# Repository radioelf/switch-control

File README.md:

# switch-control

switch-control/Crossover switch (Kicad Versión: 5.99.0, release build)

Interruptor, conmutador (doble), cruzamiento, controlado con un modulo ESP8266, lo estoy usando con Tasmota (https://github.com/arendst/Tasmota), con la siguiente configuración:
D2 GPIO4  Botón1in (126)
D1 GPIO5  Llave1n (82)
D6 GPIO12 Relé1 (21)
D7 GPIO13 Led1 (53)

Creative Commons License Disclaimer

UNLESS OTHERWISE MUTUALLY AGREED TO BY THE PARTIES IN WRITING, LICENSOR OFFERS THE WORK AS-IS AND MAKES NO REPRESENTATIONS OR WARRANTIES OF ANY KIND CONCERNING THE WORK, EXPRESS, IMPLIED, STATUTORY OR OTHERWISE, INCLUDING, WITHOUT LIMITATION, WARRANTIES OF TITLE, MERCHANTIBILITY, FITNESS FOR A PARTICULAR PURPOSE, NONINFRINGEMENT, OR THE ABSENCE OF LATENT OR OTHER DEFECTS, ACCURACY, OR THE PRESENCE OF ABSENCE OF ERRORS, WHETHER OR NOT DISCOVERABLE. SOME JURISDICTIONS DO NOT ALLOW THE EXCLUSION OF IMPLIED WARRANTIES, SO SUCH EXCLUSION MAY NOT APPLY TO YOU. EXCEPT TO THE EXTENT REQUIRED BY APPLICABLE LAW, IN NO EVENT WILL LICENSOR BE LIABLE TO YOU ON ANY LEGAL THEORY FOR ANY SPECIAL, INCIDENTAL, CONSEQUENTIAL, PUNITIVE OR EXEMPLARY DAMAGES ARISING OUT OF THIS LICENSE OR THE USE OF THE WORK, EVEN IF LICENSOR HAS BEEN ADVISED OF THE POSSIBILITY OF SUCH DAMAGES.

http://creativecommons.org/licenses/by-sa/3.0/

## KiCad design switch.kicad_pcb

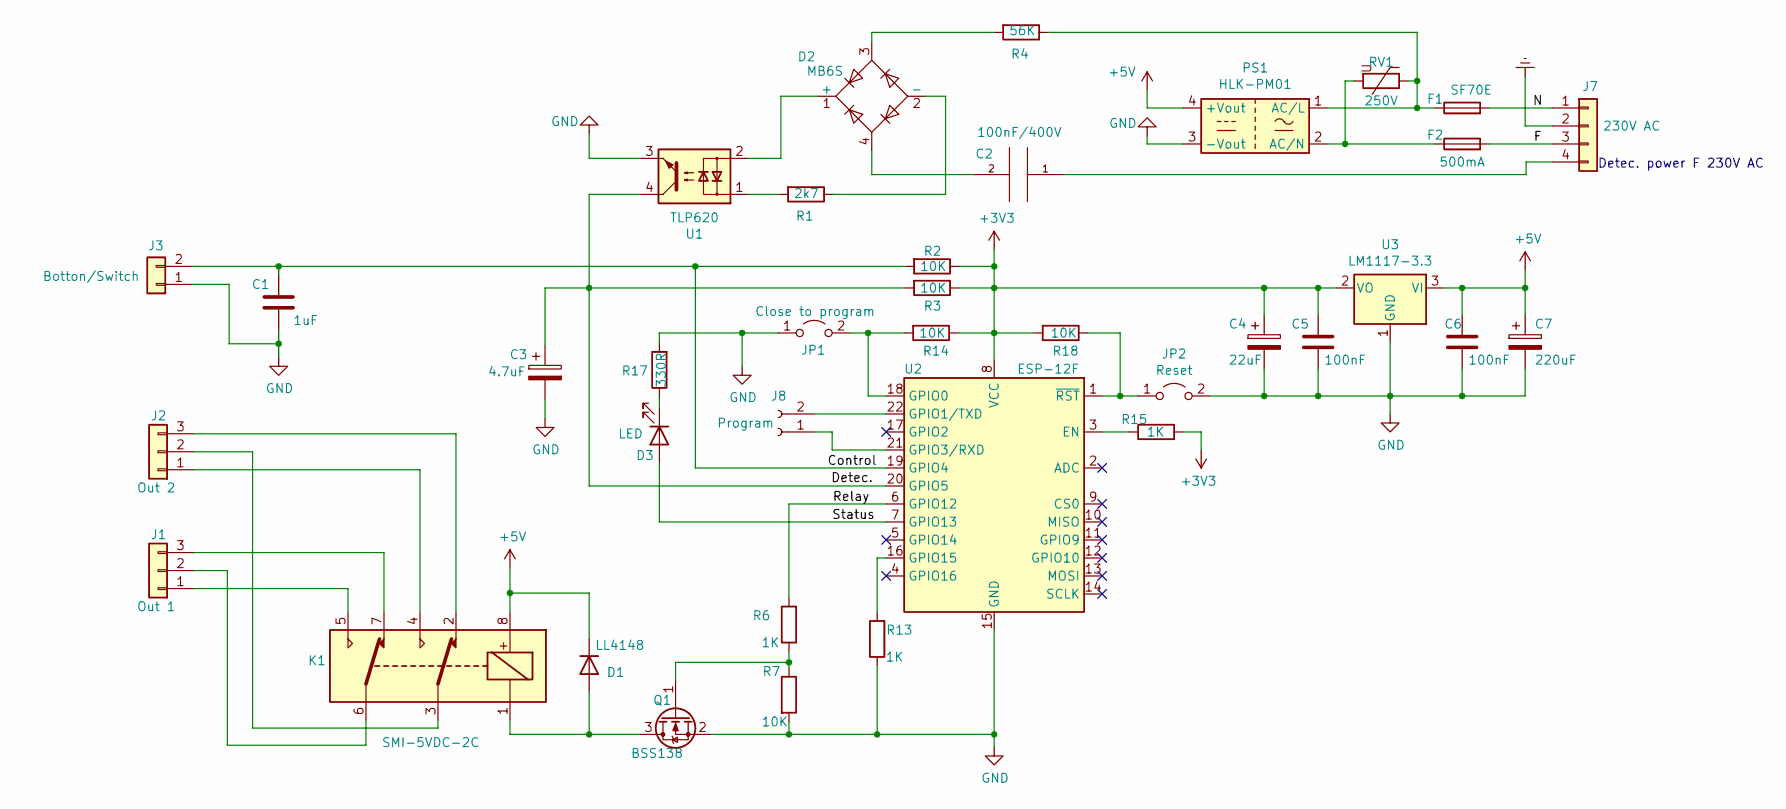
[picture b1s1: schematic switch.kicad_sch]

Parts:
C1: 1uF; C_1210_3225Metric
C2: 100nF/400V; C_Disc_D16.0mm_W5.0mm_P10.00mm
C3: 4.7uF; CP_Elec_4x3.9
C4: 22uF; CP_Elec_4x5.8
C5, C6: 100nF; L_0805_2012Metric_Pad1.15x1.40mm_HandSolder
C7: 220uF; CP_Elec_5x4.4
D1: LL4148; D_MiniMELF
D2: MB6S; TO-269AA
D3: LED; LED_0805_2012Metric
F1: SF70E; Fuse_Bourns_MF-RG400
F2: 500mA; R_Axial_DIN0207_L6.3mm_D2.5mm_P7.62mm_Horizontal
J1: Out 1; JST_NV_B03P-NV_1x03_P5.00mm_Vertical
J2: Out 2; JST_NV_B03P-NV_1x03_P5.00mm_Vertical
J3: Botton/Switch; JST_NV_B02P-NV_1x02_P5.00mm_Vertical
J7: 230V AC; JST_NV_B04P-NV_1x04_P5.00mm_Vertical
J8: Program; PinHeader_1x02_P2.54mm_Vertical
JP1: Close to program; PinHeader_1x02_P2.54mm_Vertical
JP2: Reset; PinHeader_1x02_P2.54mm_Vertical
K1: SMI-5VDC-2C; Relay_DPDT_Omron_G2RL
PS1: HLK-PM01; Converter_ACDC_HiLink_HLK-PMxx
Q1: BSS138; SOT-23
R1: 2k7; R_0805_2012Metric
R2, R3, R7, R14, R18: 10K; R_0805_2012Metric
R4: 56K; R_0805_2012Metric
R6, R13, R15: 1K; R_0805_2012Metric
R17: 330R; R_0805_2012Metric
RV1: 250V; RV_Disc_D12mm_W3.9mm_P7.5mm
U1: TLP620; DIP-4_W7.62mm_Socket_LongPads
U2: ESP-12F; ESP-12E
U3: LM1117-3.3; SOT-223-3_TabPin2

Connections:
+3V3: C4.1, C5.2, R2.1, R3.1, R14.1, R15.2, R18.2, U2.8 (VCC), U3.2 (VO)
+5V: C6.2, C7.1, D1.1 (K), K1.8, PS1.4 (+Vout), U3.3 (VI)
/Control: C1.2, J3.2, R2.2, U2.19 (GPIO4)
/F: F2.2, J7.3
/N: F1.2, J7.1
/Relay: R6.2, U2.6 (GPIO12)
/Status: D3.2 (A), U2.7 (GPIO13)
Earth: J7.2
GND: C1.1, C3.2, C4.2, C5.1, C6.1, C7.2, J3.1, JP1.1 (A), JP2.2 (B), PS1.3 (-Vout), Q1.2 (S), R7.2, R13.1, R17.2, U1.3, U2.15 (GND), U3.1 (GND)
unnamed: C2.1, J7.4
unnamed: C2.2, D2.4 (~~)
unnamed: C3.1, R3.2, U1.4, U2.20 (GPIO5)
unnamed: D1.2 (A), K1.1, Q1.3 (D)
unnamed: D2.1 (+), U1.2
unnamed: D2.2 (-), R1.1
unnamed: D2.3 (~~), R4.2
unnamed: D3.1 (K), R17.1
unnamed: F1.1, PS1.1 (AC/L), R4.1, RV1.1
unnamed: F2.1, PS1.2 (AC/N), RV1.2
unnamed: J1.1, K1.5
unnamed: J1.2, K1.6
unnamed: J1.3, K1.7
unnamed: J2.1, K1.4
unnamed: J2.2, K1.3
unnamed: J2.3, K1.2
unnamed: J8.1, U2.21 (GPIO3/RXD)
unnamed: J8.2, U2.22 (GPIO1/TXD)
unnamed: JP1.2 (B), R14.2, U2.18 (GPIO0)
unnamed: JP2.1 (A), R18.1, U2.1 (~RST)
unnamed: Q1.1 (G), R6.1, R7.1
unnamed: R1.2, U1.1
unnamed: R13.2, U2.16 (GPIO15)
unnamed: R15.1, U2.3 (EN)

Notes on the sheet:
Detec. power F 230V AC

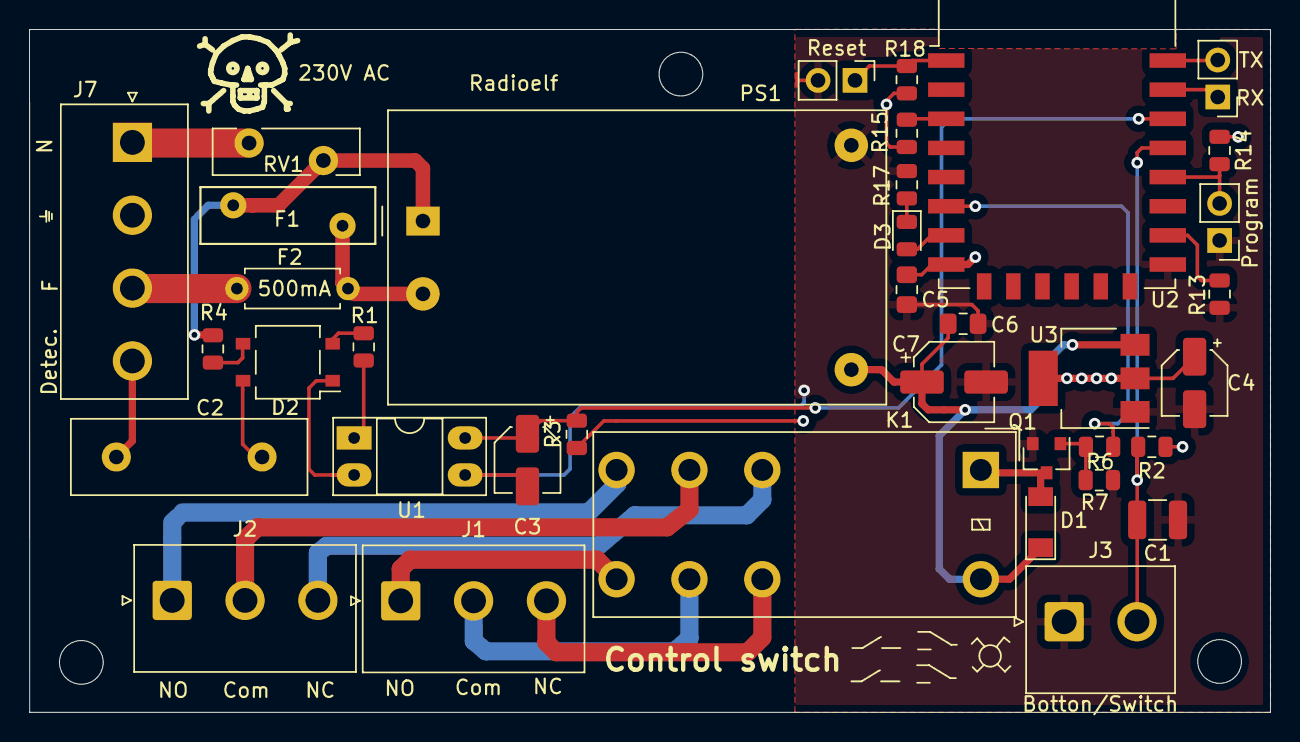
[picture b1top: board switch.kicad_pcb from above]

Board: 2 copper layers, 85.2 x 46.9 mm, 37 parts (0 on the bottom side), 32 nets.
